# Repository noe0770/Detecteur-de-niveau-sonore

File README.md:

# Détecteur de niveau sonore

Le but de ce projet est de concevoir un détecteur de niveau sonore. Il permet de mesurer en dB(A) le niveau sonore moyen de l'environnement, et d'en afficher la valeur, sur l'interface graphique en ligne Grafana via Wi-Fi, et via un niveau de LEDs de couleurs (vert, orange, rouge). Un microphone à condensateur électret a été utilisé, et le conditionnement du signal analogique (amplification et filtrage), ainsi que l'étalonnage de ce dernier ont été effectués. Le tout a été réalisé sous forme de carte électronique au format shield pour ESP32. Un emplacement pour un microphone Grove a été laissé sur la carte. Le détail de tout le projet est présenté dans le rapport fourni.

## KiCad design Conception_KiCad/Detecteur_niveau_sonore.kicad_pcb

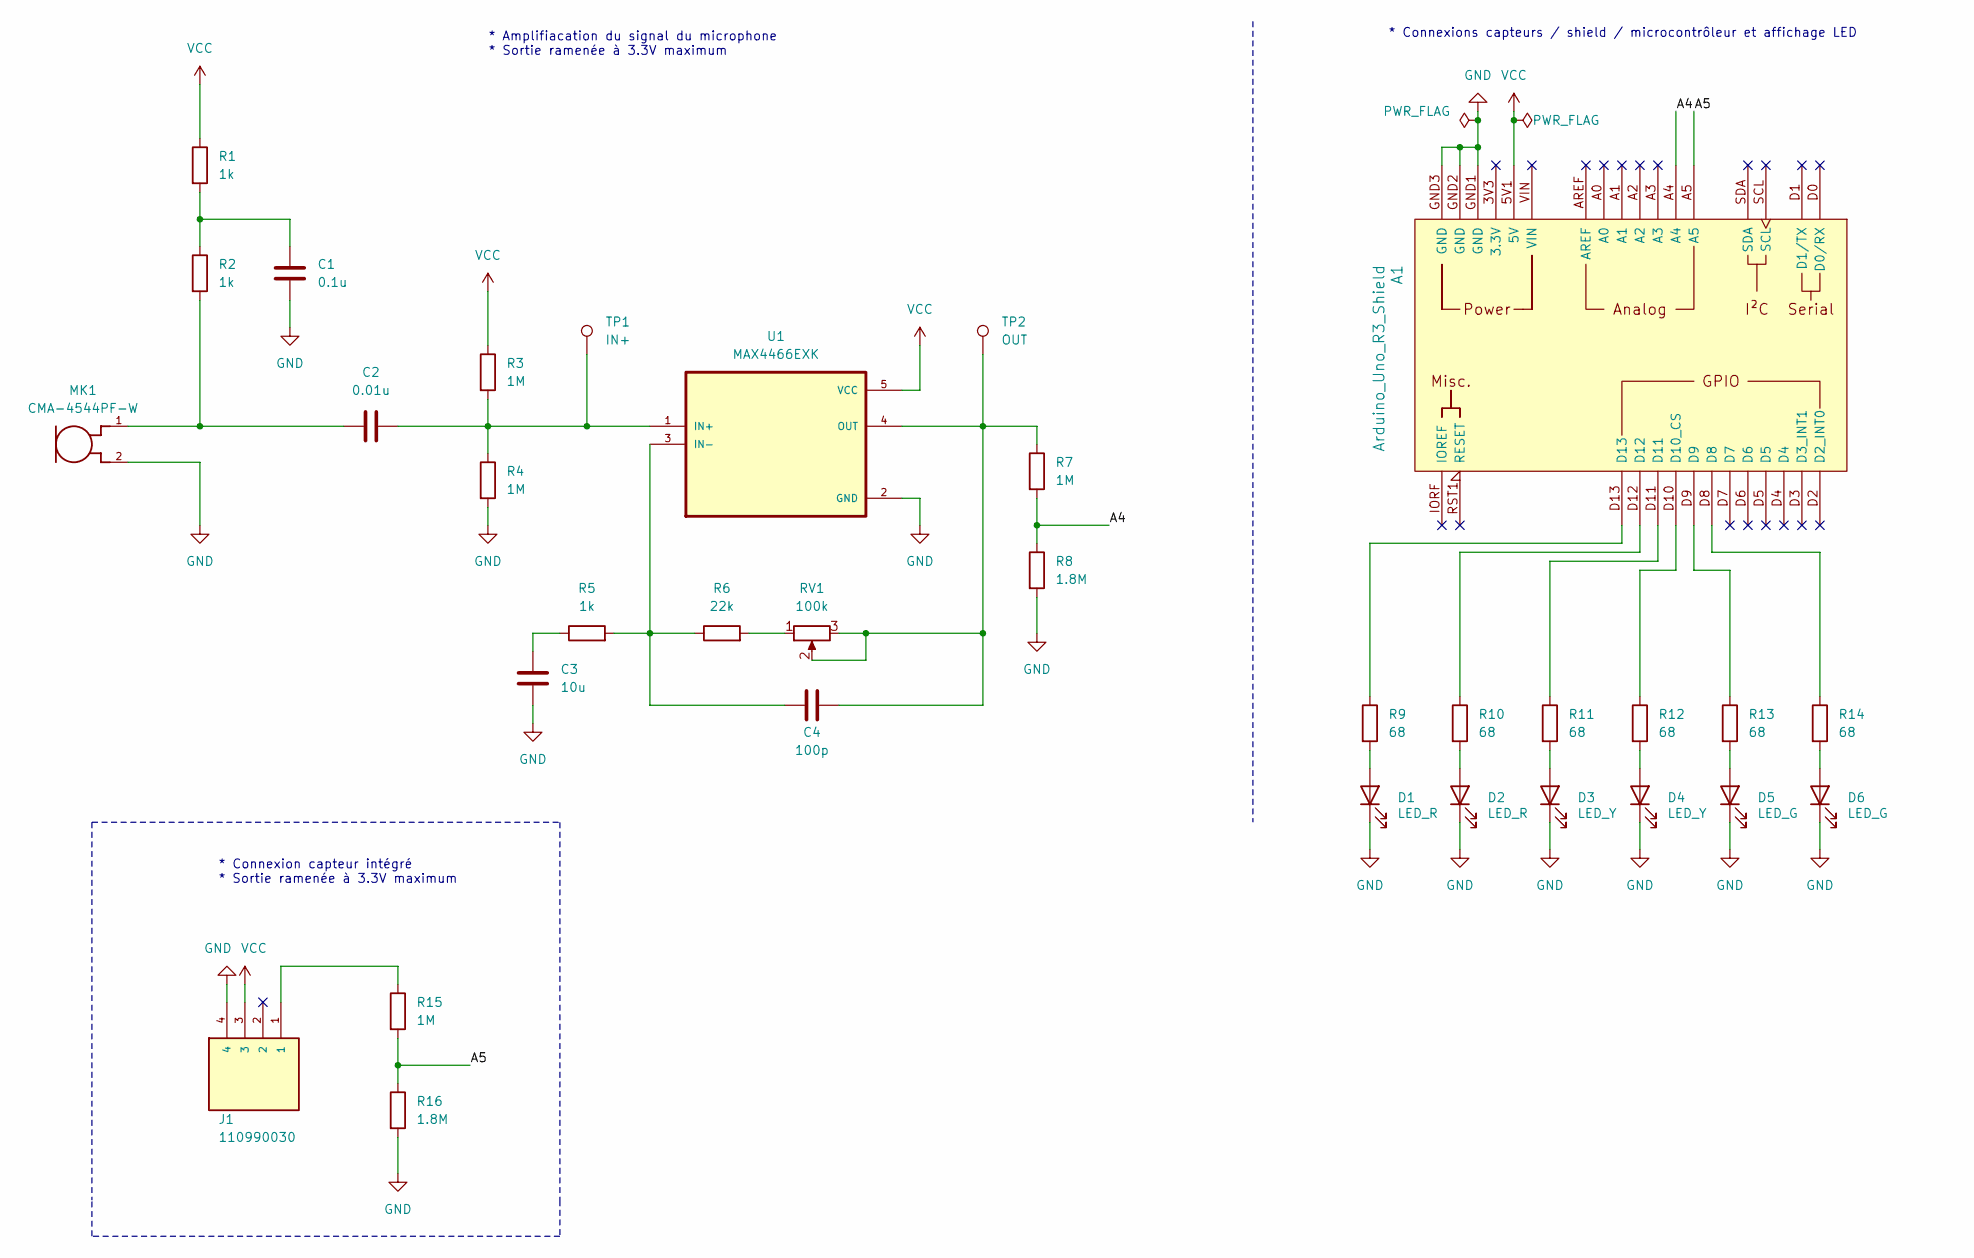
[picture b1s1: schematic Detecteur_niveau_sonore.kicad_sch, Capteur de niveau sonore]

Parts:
A1: Arduino_Uno_R3_Shield; Arduino_Uno_R3_Shield_EDIT
C1: 0.1u; C_0805_2012Metric_Pad1.18x1.45mm_HandSolder
C2: 0.01u; C_0805_2012Metric_Pad1.18x1.45mm_HandSolder
C3: 10u; C_0805_2012Metric_Pad1.18x1.45mm_HandSolder
C4: 100p; C_0805_2012Metric_Pad1.18x1.45mm_HandSolder
D1, D2: LED_R; LED_0805_2012Metric_Pad1.15x1.40mm_HandSolder
D3, D4: LED_Y; LED_0805_2012Metric_Pad1.15x1.40mm_HandSolder
D5, D6: LED_G; LED_0805_2012Metric_Pad1.15x1.40mm_HandSolder
J1: 110990030; SEEED_110990030; PARTREV A
MK1: CMA-4544PF-W; MIC_CMA-4544PF-W
R1, R2, R5: 1k; R_0805_2012Metric_Pad1.20x1.40mm_HandSolder
R3, R4, R7, R15: 1M; R_0805_2012Metric_Pad1.20x1.40mm_HandSolder
R6: 22k; R_0805_2012Metric_Pad1.20x1.40mm_HandSolder
R8, R16: 1.8M; R_0805_2012Metric_Pad1.20x1.40mm_HandSolder
R9, R10, R11, R12, R13, R14: 68; R_0805_2012Metric_Pad1.20x1.40mm_HandSolder
RV1: 100k; Potentiometer_Bourns_3314J_Vertical
TP1: IN+; TestPoint_Pad_D2.5mm
TP2: OUT; TestPoint_Pad_D2.5mm
U1: MAX4466EXK; SOT65P210X110-5N

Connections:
/A4: A1.A4, R7.2, R8.1
/A5: A1.A5, R15.2, R16.1
GND: A1.GND1 (GND), A1.GND2 (GND), A1.GND3 (GND), C1.2, C3.2, D1.1 (K), D2.1 (K), D3.1 (K), D4.1 (K), D5.1 (K), D6.1 (K), J1.4, MK1.2, R4.2, R8.2, R16.2, U1.2 (GND)
unnamed: A1.D10 (D10_CS), R12.1
unnamed: A1.D8, R14.1
unnamed: A1.D9, R13.1
unnamed: A1.D11, R11.1
unnamed: A1.D12, R10.1
unnamed: A1.D13, R9.1
unnamed: C1.1, R1.2, R2.1
unnamed: C2.2, MK1.1, R2.2
unnamed: C3.1, R5.1
unnamed: D1.2 (A), R9.2
unnamed: D2.2 (A), R10.2
unnamed: D3.2 (A), R11.2
unnamed: D4.2 (A), R12.2
unnamed: D5.2 (A), R13.2
unnamed: D6.2 (A), R14.2
unnamed: J1.1, R15.1
unnamed: R6.2, RV1.1
unnamed: C2.1, R3.2, R4.1, TP1.1, U1.1 (IN+)
unnamed: C4.1, R5.2, R6.1, U1.3 (IN-)
unnamed: C4.2, R7.1, RV1.2, RV1.3, TP2.1, U1.4 (OUT)
VCC: A1.5V1 (5V), J1.3, R1.1, R3.1, U1.5 (VCC)

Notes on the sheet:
* Connexion capteur intégré * Sortie ramenée à 3.3V maximum
* Amplifiacation du signal du microphone * Sortie ramenée à 3.3V maximum
* Connexions capteurs / shield / microcontrôleur et affichage LED

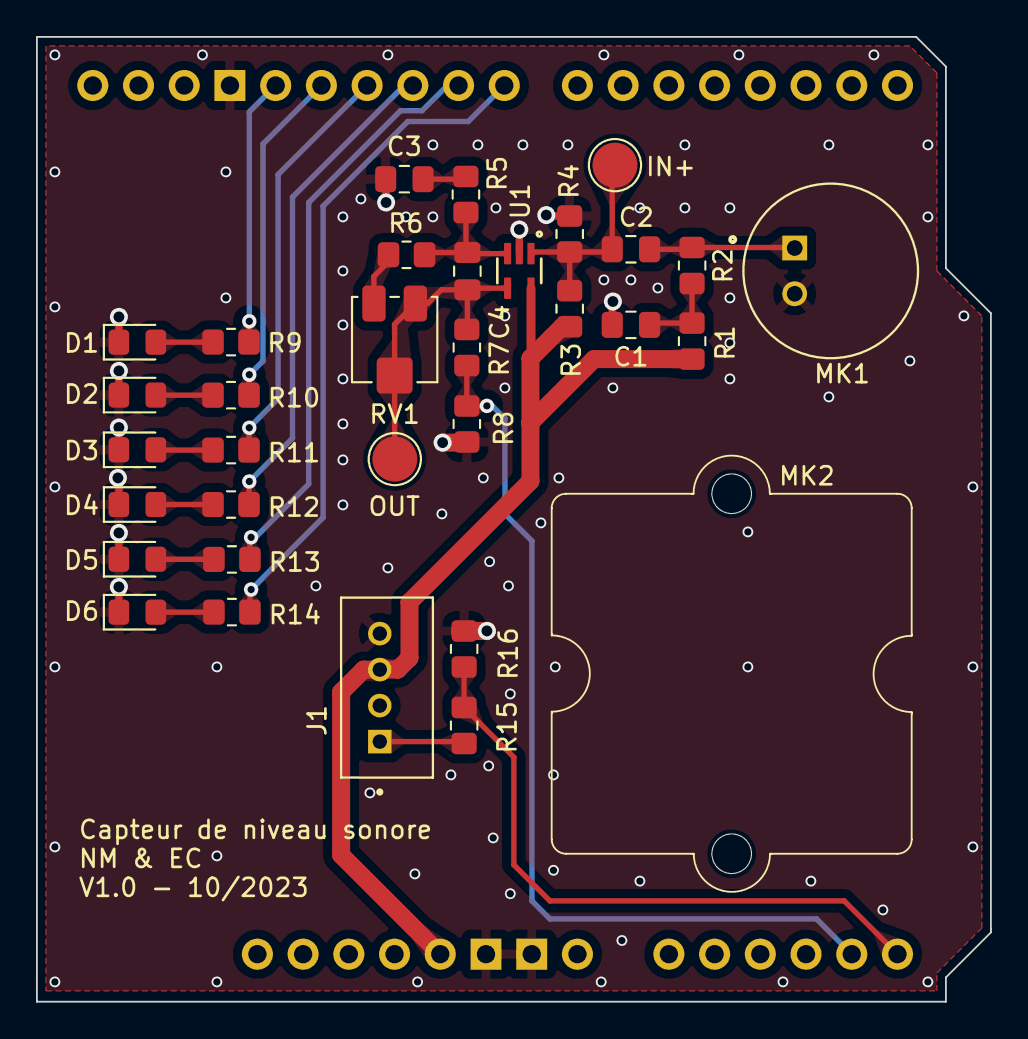
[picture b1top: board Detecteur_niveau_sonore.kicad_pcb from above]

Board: 2 copper layers, 53.0 x 53.6 mm, 34 parts (0 on the bottom side), 24 nets.

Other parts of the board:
MK2: Grove_loudness_sensor_EDIT
